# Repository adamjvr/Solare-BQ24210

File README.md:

# Solare-BQ24210
Solare-BQ24210 is a solar Lithium Battery charger based on the BQ24210 battery charge controller from Ti

Solare-BQ24210 PCB

KiCAD 3D Render

OSHPark Render

OSHPark PCBs 10/19/2016

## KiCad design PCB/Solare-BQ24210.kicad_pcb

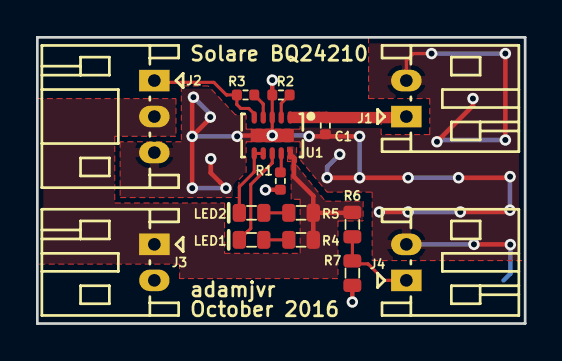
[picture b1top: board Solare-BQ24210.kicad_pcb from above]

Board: 2 copper layers, 27.1 x 15.9 mm, 15 parts (0 on the bottom side), 12 nets.

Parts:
C1: CL05A105KA5NQNC; C0402
J1, J3, J4: S2B-PH-K-S(LF)(SN)
J2: S3B-PH-K-S(LF)(SN)
LED1: LTST-C191KGKT; LED0603
LED2: LTST-C191KFKT; LED0603
R1, R3: RC1005F102CS; R0402
R2: RC1005F4870CS; R0402
R4, R5: RC1608J202CS; R0603
R6, R7: ERA-3AEB3741V; R0603
U1: BQ24210DQCT; BQ24210

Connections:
/BAT: J2.2, J3.1, R4.2, R5.2, R6.1, U1.10
/BAT_VOLT: J4.1, R6.2, R7.1
/THERM: J2.1, R3.2, U1.5
GND: C1.2, J1.2, J2.3, J3.2, J4.2, R1.2, R2.2, R7.2, U1.3, U1.11
unnamed: C1.1, J1.1, U1.1
unnamed: LED1.1, R4.1
unnamed: LED1.2, U1.8
unnamed: LED2.1, R5.1
unnamed: LED2.2, U1.6, U1.7
unnamed: R1.1, U1.9
unnamed: R2.1, U1.2
unnamed: R3.1, U1.4

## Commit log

2016-10-02 Initial COmmit
    Initial Commit, board complete, schematic and PCB. pending some final
    checks before ordering.
2016-10-02 Images
    Images added
2016-10-02 3D
    3D models added to connectors, and 3D render image added.
2016-10-14 ReadMe
    Readme and pictures edited
2016-10-14 Readme
    Readme quickfix
2016-10-20 Readme and Image
    Readme updated. added image of fabricated PCBs
2016-10-20 Image fix
    Fixing image in readem
2016-10-21 License
    CERN open hardware license added.
